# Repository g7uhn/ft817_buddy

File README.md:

# ft817_buddy
A companion display &amp; controls for the FT-817.

This is a work in progess, [more information at my page](http://alloutput.com/ft-817-buddy/).

A little story about the build is over at [SWLing Post](https://swling.com/blog/2020/08/andy-builds-a-genius-companion-control-display-for-the-yaesu-ft-817-transceiver/).

Rev4 hardware files now released :-)

Enjoy!

<br />This work is licensed under a <a rel="license" href="http://creativecommons.org/licenses/by-sa/4.0/">Creative Commons Attribution-ShareAlike 4.0 International License</a>.

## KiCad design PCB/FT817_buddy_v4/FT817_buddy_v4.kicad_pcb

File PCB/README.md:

Rev4 hardware files

<br />This work is licensed under a <a rel="license" href="http://creativecommons.org/licenses/by-sa/4.0/">Creative Commons Attribution-ShareAlike 4.0 International License</a>.

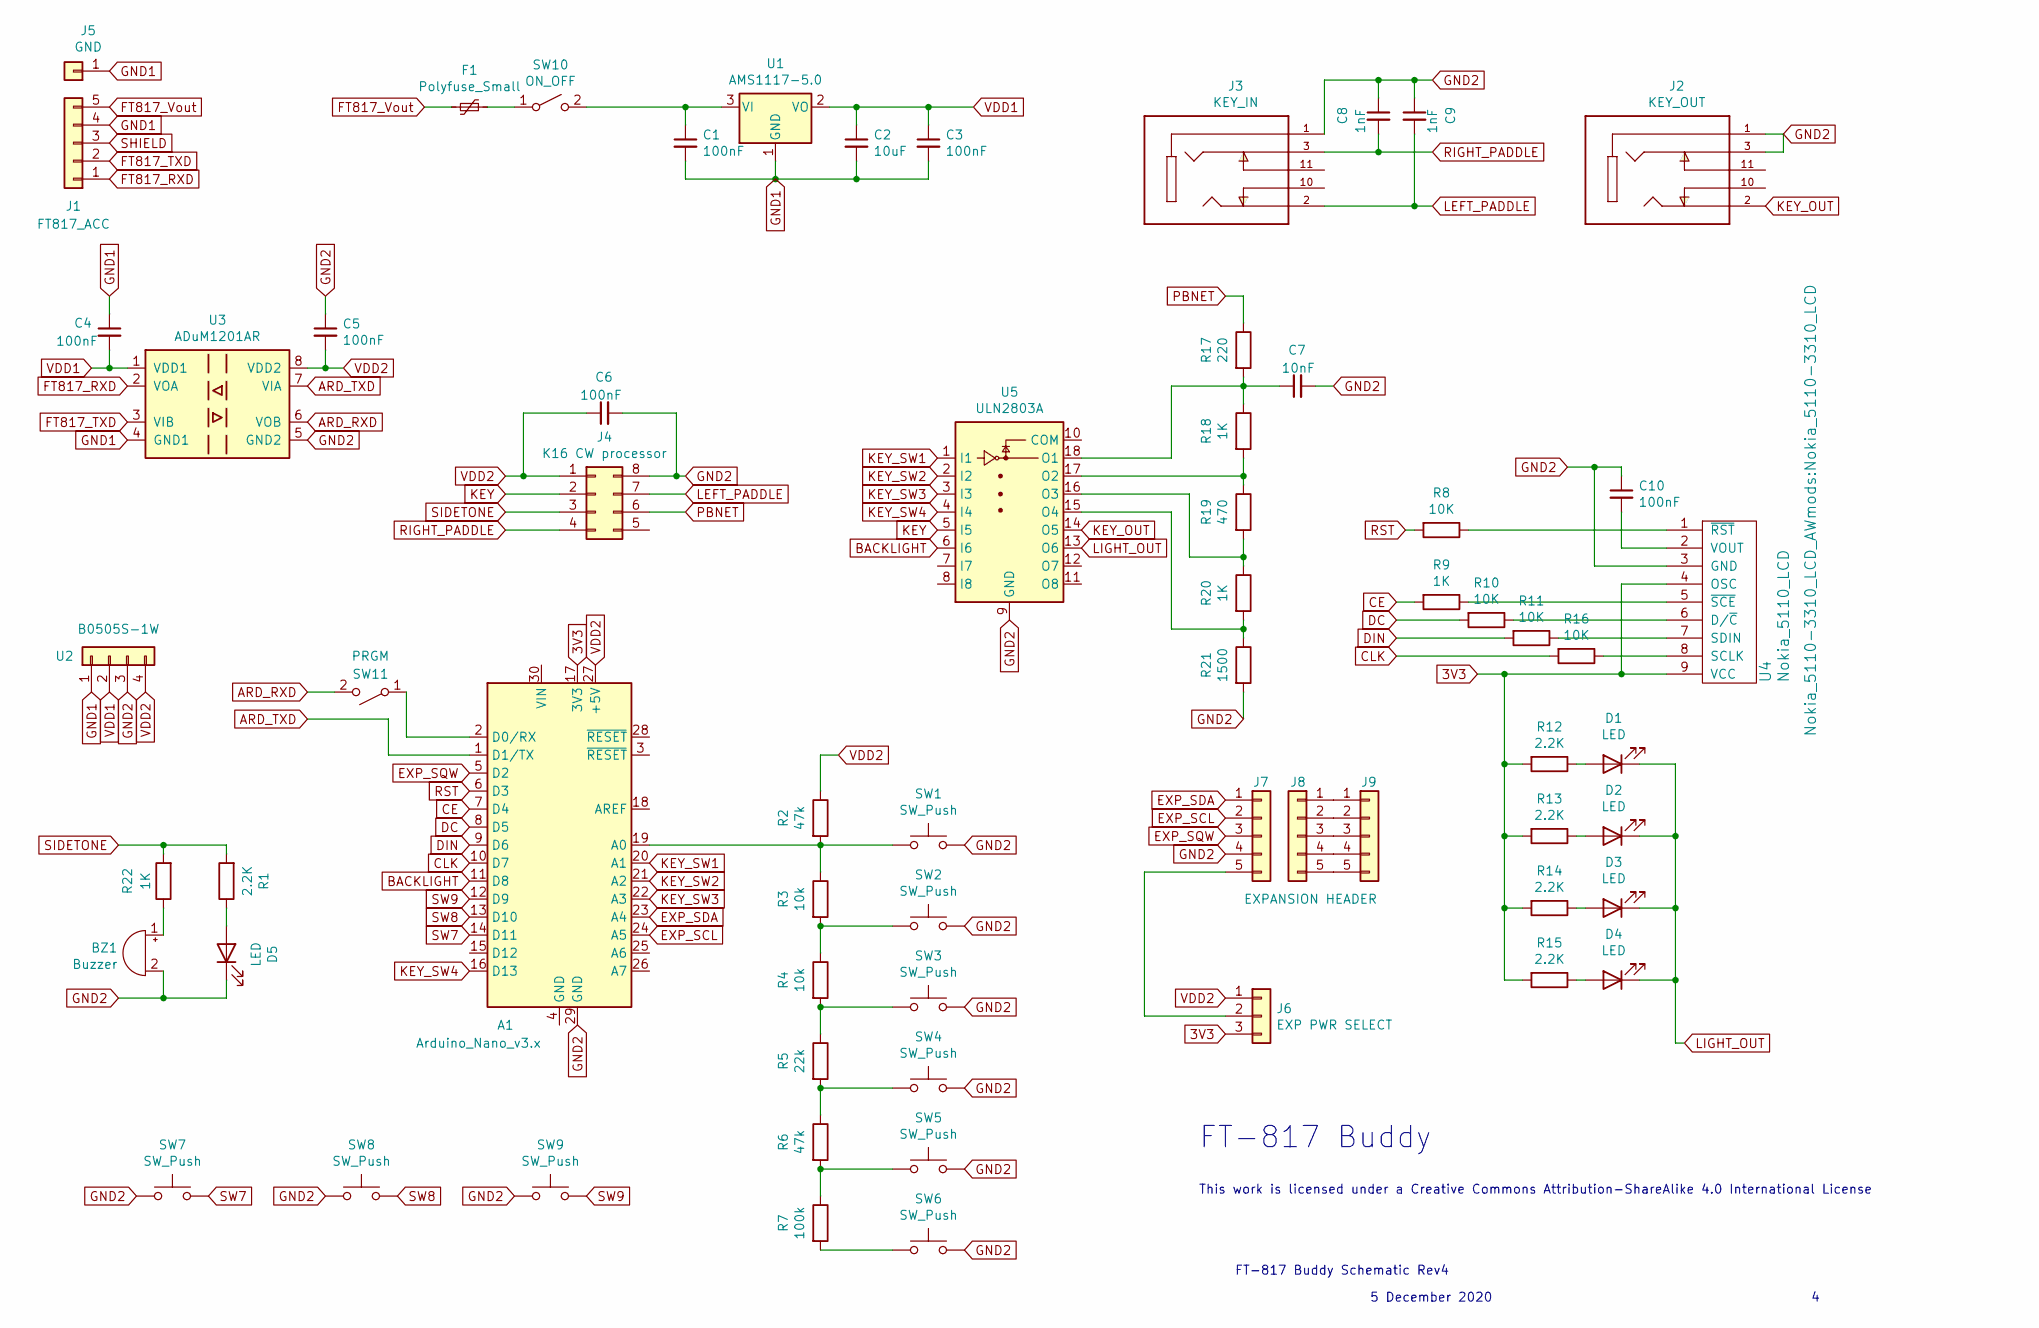
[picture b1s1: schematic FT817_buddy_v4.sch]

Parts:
A1: Arduino_Nano_v3.x; Arduino_Nano
BZ1: Buzzer; Buzzer_Murata_PKMCS0909E4000-R1
C1, C3, C4, C5, C6, C10: 100nF; C_0805_2012Metric_Pad1.15x1.40mm_HandSolder; JLCPCB C49678
C2: 10uF; C_0805_2012Metric_Pad1.15x1.40mm_HandSolder; JLCPCB C15850
C7: 10nF; C_0805_2012Metric_Pad1.15x1.40mm_HandSolder; JLCPCB C1710
C8, C9: 1nF; C_0805_2012Metric_Pad1.15x1.40mm_HandSolder; JLCPCB C46653
D1, D2, D3, D4, D5: LED; LED_0805_2012Metric_Pad1.15x1.40mm_HandSolder
F1: Polyfuse_Small; Fuse_1206_3216Metric_Pad1.42x1.75mm_HandSolder; JLCPCB C369154
J1: FT817_ACC; PinHeader_1x05_P2.54mm_Horizontal
J2: KEY_OUT; CUI_SJ1-3525N; PARTREV 1.02
J3: KEY_IN; CUI_SJ1-3525N; PARTREV 1.02
J4: K16 CW processor; DIP-8_W7.62mm_Socket
J5: GND; PinHeader_1x01_P2.54mm_Vertical
J6: EXP PWR SELECT; PinHeader_1x03_P2.54mm_Vertical
J7, J8: PinHeader_1x05_P2.54mm_Vertical
J9: EXPANSION HEADER; PinSocket_1x05_P2.54mm_Vertical
R1, R12, R13, R14, R15: 2.2K; R_0805_2012Metric_Pad1.15x1.40mm_HandSolder; JLCPCB C17520
R2, R6: 47k; R_0805_2012Metric_Pad1.15x1.40mm_HandSolder; JLCPCB C17713
R3, R4: 10k; R_0805_2012Metric_Pad1.15x1.40mm_HandSolder; JLCPCB C17414
R5: 22k; R_0805_2012Metric_Pad1.15x1.40mm_HandSolder; JLCPCB C17560
R7: 100k; R_0805_2012Metric_Pad1.15x1.40mm_HandSolder; JLCPCB C17407
R8, R10, R11, R16: 10K; R_0805_2012Metric_Pad1.15x1.40mm_HandSolder; JLCPCB C17414
R9, R18, R20, R22: 1K; R_0805_2012Metric_Pad1.15x1.40mm_HandSolder; JLCPCB C17513
R17: 220; R_0805_2012Metric_Pad1.15x1.40mm_HandSolder; JLCPCB C17557
R19: 470; R_0805_2012Metric_Pad1.15x1.40mm_HandSolder; JLCPCB C17710
R21: 1500; R_0805_2012Metric_Pad1.15x1.40mm_HandSolder; JLCPCB C4310
SW1, SW2, SW3, SW4, SW5, SW6, SW7, SW8, SW9: SW_Push; SW_PUSH_6mm
SW10: ON_OFF; SW_Slide_1P2T_CK_OS102011MS2Q
SW11: PRGM; SW_Slide_1P2T_CK_OS102011MS2Q
U1: AMS1117-5.0; SOT-223-3_TabPin2; JLCPCB C6187
U2: B0505S-1W; PinHeader_1x04_P2.54mm_Vertical
U3: ADuM1201AR; SOIC-8_3.9x4.9mm_P1.27mm; JLCPCB C9669
U4: Nokia_5110_LCD; Nokia_5110-3310_LCD
U5: ULN2803A; SOIC-18W_7.5x11.6mm_P1.27mm; JLCPCB C9683

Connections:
3V3: A1.17 (3V3), J6.3, R12.2, R13.2, R14.2, R15.2, U4.4 (OSC), U4.9 (VCC)
ARD_RXD: SW11.2 (B), U3.6 (VOB)
ARD_TXD: A1.1 (D1/TX), U3.7 (VIA)
BACKLIGHT: A1.11 (D8), U5.6 (I6)
CE: A1.7 (D4), R9.2
CLK: A1.10 (D7), R16.2
DC: A1.8 (D5), R10.2
DIN: A1.9 (D6), R11.2
EXP_SCL: A1.24 (A5), J7.2
EXP_SDA: A1.23 (A4), J7.1
EXP_SQW: A1.5 (D2), J7.3
FT817_RXD: J1.1, U3.2 (VOA)
FT817_TXD: J1.2, U3.3 (VIB)
FT817_Vout: F1.2, J1.5
GND1: C1.2, C2.2, C3.2, C4.1, J1.4, J5.1, U1.1 (GND), U2.1, U3.4 (GND1)
GND2: A1.29 (GND), BZ1.2 (+), C5.1, C6.2, C7.2, C8.1, C9.1, C10.1, D5.1 (K), J2.1, J2.3, J3.1, J4.8, J7.4, R21.2, SW1.2, SW2.2, SW3.2, SW4.1, SW5.1, SW6.1, SW7.1, SW8.1, SW9.1, U2.3, U3.5 (GND2), U4.3 (GND), U5.9 (GND)
KEY: J4.2, U5.5 (I5)
KEY_OUT: J2.2, U5.14 (O5)
KEY_SW1: A1.20 (A1), U5.1 (I1)
KEY_SW2: A1.21 (A2), U5.2 (I2)
KEY_SW3: A1.22 (A3), U5.3 (I3)
KEY_SW4: A1.16 (D13), U5.4 (I4)
LEFT_PADDLE: C9.2, J3.2, J4.7
LIGHT_OUT: D1.1 (K), D2.1 (K), D3.1 (K), D4.1 (K), U5.13 (O6)
unnamed: A1.2 (D0/RX), SW11.1 (A)
unnamed: A1.19 (A0), R2.2, R3.1, SW1.1
unnamed: BZ1.1 (-), R22.1
unnamed: C1.1, SW10.2 (B), U1.3 (VI)
unnamed: C7.1, R17.2, R18.1, U5.18 (O1)
unnamed: C10.2, U4.2 (VOUT)
unnamed: D1.2 (A), R12.1
unnamed: D2.2 (A), R13.1
unnamed: D3.2 (A), R14.1
unnamed: D4.2 (A), R15.1
unnamed: D5.2 (A), R1.1
unnamed: F1.1, SW10.1 (A)
unnamed: J6.2, J7.5
unnamed: J8.1, J9.1
unnamed: J8.2, J9.2
unnamed: J8.3, J9.3
unnamed: J8.4, J9.4
unnamed: J8.5, J9.5
unnamed: R3.2, R4.1, SW2.1
unnamed: R4.2, R5.1, SW3.1
unnamed: R5.2, R6.1, SW4.2
unnamed: R6.2, R7.1, SW5.2
unnamed: R7.2, SW6.2
unnamed: R8.1, U4.1 (~RST)
unnamed: R9.1, U4.5 (~SCE)
unnamed: R10.1, U4.6 (D/~C)
unnamed: R11.1, U4.7 (SDIN)
unnamed: R16.1, U4.8 (SCLK)
unnamed: R18.2, R19.1, U5.17 (O2)
unnamed: R19.2, R20.1, U5.16 (O3)
unnamed: R20.2, R21.1, U5.15 (O4)
PBNET: J4.6, R17.1
RIGHT_PADDLE: C8.2, J3.3, J4.4
RST: A1.6 (D3), R8.2
SHIELD: J1.3
SIDETONE: J4.3, R1.2, R22.2
SW7: A1.14 (D11), SW7.2
SW8: A1.13 (D10), SW8.2
SW9: A1.12 (D9), SW9.2
VDD1: C2.1, C3.1, C4.2, U1.2 (VO), U2.2, U3.1 (VDD1)
VDD2: A1.27 (+5V), C5.2, C6.1, J4.1, J6.1, R2.1, U2.4, U3.8 (VDD2)

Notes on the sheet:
This work is licensed under a Creative Commons Attribution-ShareAlike 4.0 International License
FT-817 Buddy Schematic Rev4
5 December 2020
FT-817 Buddy

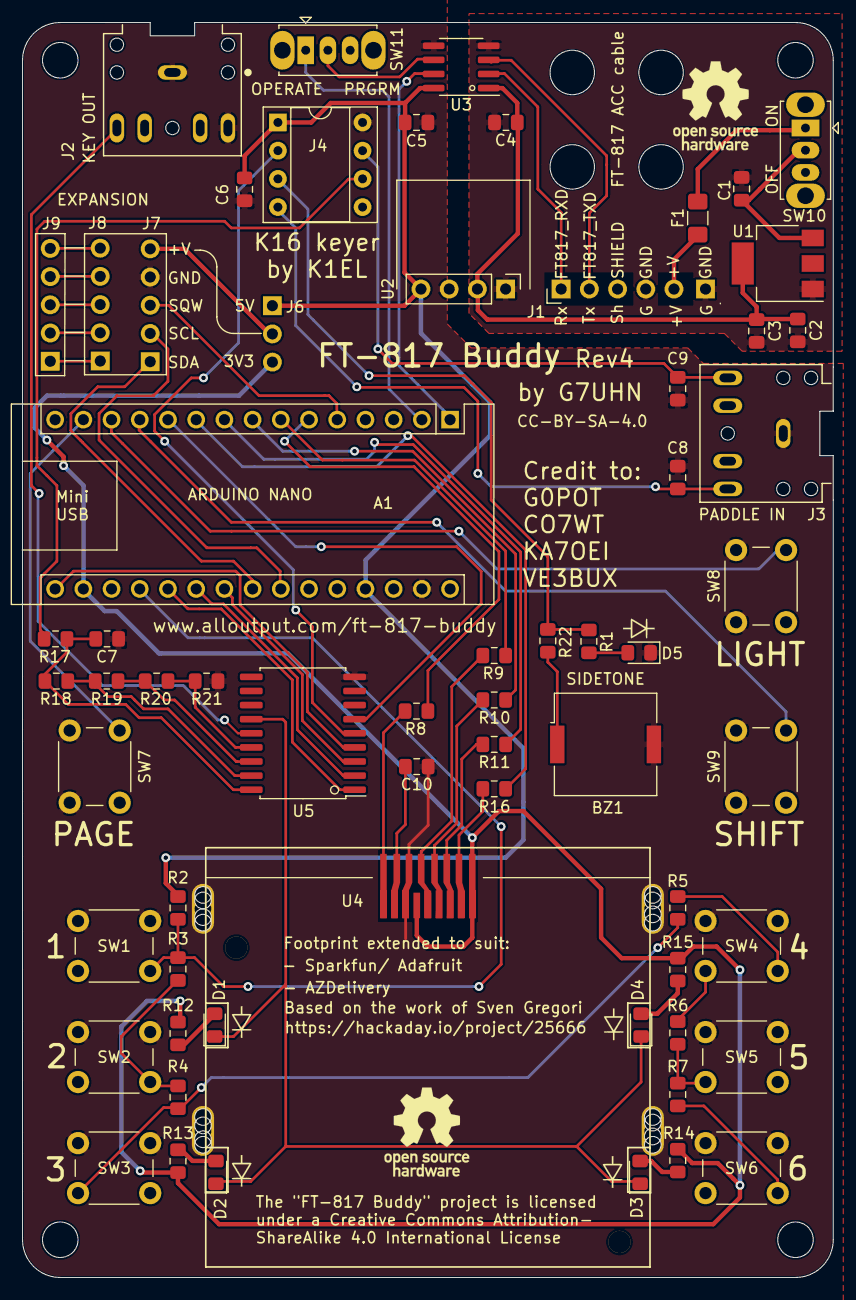
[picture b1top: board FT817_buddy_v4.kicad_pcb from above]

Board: 2 copper layers, 73.0 x 113.0 mm, 70 parts (0 on the bottom side), 64 nets.

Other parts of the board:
 : diode_small
 #2,  #3,  #4,  #5: diode_small

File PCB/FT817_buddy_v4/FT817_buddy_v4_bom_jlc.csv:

"Comment","Designator","Footprint","LCSC Part #"
"100nF","C1,C3,C5,C4,C10,C6","C_0805_2012Metric_Pad1.15x1.40mm_HandSolder","C49678"
"10uF","C2","C_0805_2012Metric_Pad1.15x1.40mm_HandSolder","C15850"
"10nF","C7","C_0805_2012Metric_Pad1.15x1.40mm_HandSolder","C1710"
"1nF","C8,C9","C_0805_2012Metric_Pad1.15x1.40mm_HandSolder","C46653"
"Polyfuse_Small","F1","Fuse_1206_3216Metric_Pad1.42x1.75mm_HandSolder","C369154"
"47k","R2,R6","R_0805_2012Metric_Pad1.15x1.40mm_HandSolder","C17713"
"10k","R3,R4","R_0805_2012Metric_Pad1.15x1.40mm_HandSolder","C17414"
"22k","R5","R_0805_2012Metric_Pad1.15x1.40mm_HandSolder","C17560"
"100k","R7","R_0805_2012Metric_Pad1.15x1.40mm_HandSolder","C17407"
"10K","R8,R10,R11,R16","R_0805_2012Metric_Pad1.15x1.40mm_HandSolder","C17414"
"1K","R9,R18,R20,R22","R_0805_2012Metric_Pad1.15x1.40mm_HandSolder","C17513"
"2.2K","R12,R13,R14,R15,R1","R_0805_2012Metric_Pad1.15x1.40mm_HandSolder","C17520"
"220","R17","R_0805_2012Metric_Pad1.15x1.40mm_HandSolder","C17557"
"470","R19","R_0805_2012Metric_Pad1.15x1.40mm_HandSolder","C17710"
"1500","R21","R_0805_2012Metric_Pad1.15x1.40mm_HandSolder","C4310"
"AMS1117-5.0","U1","SOT-223-3_TabPin2","C6187"
"ADuM1201AR","U3","SOIC-8_3.9x4.9mm_P1.27mm","C9669"
"ULN2803A","U5","SOIC-18W_7.5x11.6mm_P1.27mm","C9683"

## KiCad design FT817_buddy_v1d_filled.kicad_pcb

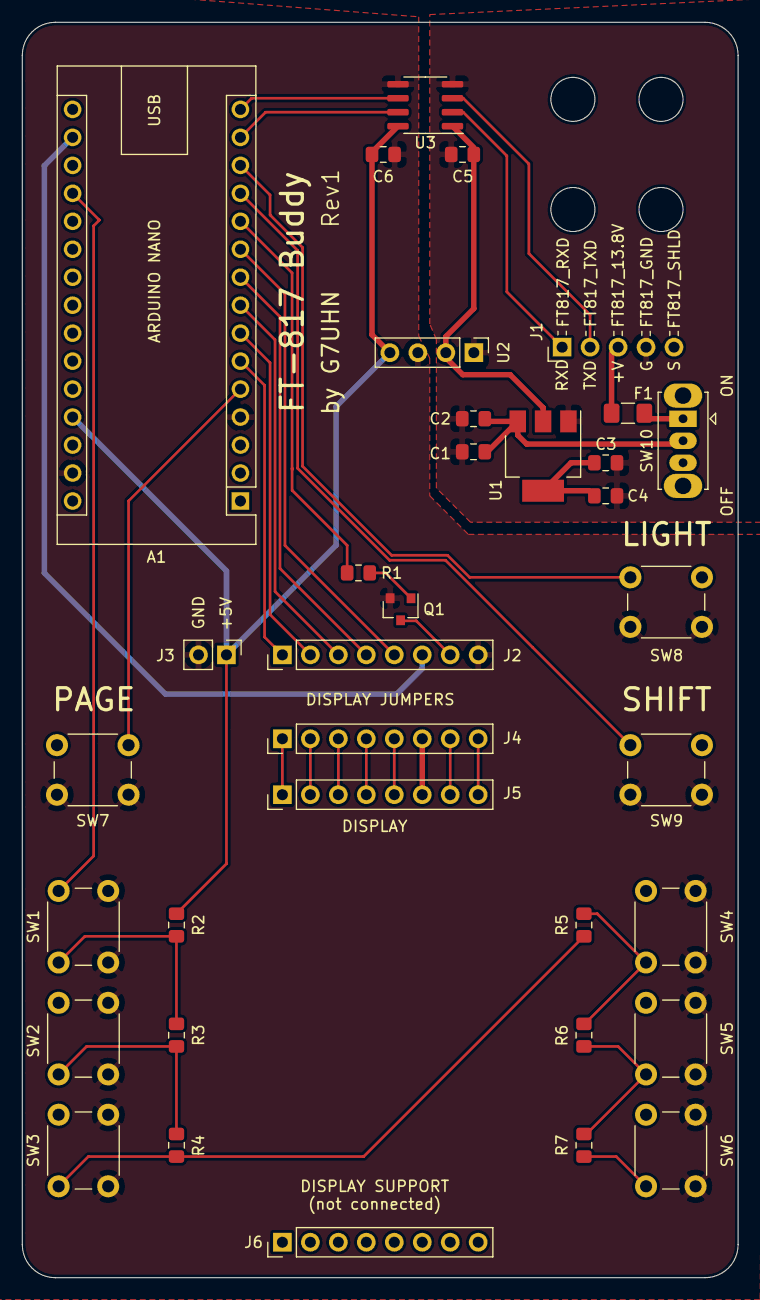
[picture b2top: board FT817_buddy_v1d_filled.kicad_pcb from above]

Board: 2 copper layers, 65.0 x 114.0 mm, 35 parts (0 on the bottom side), 37 nets.

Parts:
A1: Arduino_Nano_v3.x; Arduino_Nano
C1, C3: 10uF; C_0805_2012Metric_Pad1.15x1.40mm_HandSolder
C2, C4, C5, C6: 100nF; C_0805_2012Metric_Pad1.15x1.40mm_HandSolder
F1: Polyfuse_Small; Fuse_1206_3216Metric_Pad1.42x1.75mm_HandSolder
J1: FT817_ACC; PinHeader_1x05_P2.54mm_Horizontal
J2: ARD_SPI; PinHeader_1x08_P2.54mm_Vertical
J3: 5VDC; PinHeader_1x02_P2.54mm_Vertical
J4: DISP_PINS; PinHeader_1x08_P2.54mm_Vertical
J5: DISPLAY; PinHeader_1x08_P2.54mm_Vertical
J6: DISPLAY_SUPPORT; PinHeader_1x08_P2.54mm_Vertical
Q1: BC817; SOT-23
R1: 1k; R_0805_2012Metric_Pad1.15x1.40mm_HandSolder
R2, R6: 47k; R_0805_2012Metric_Pad1.15x1.40mm_HandSolder
R3: 9k1; R_0805_2012Metric_Pad1.15x1.40mm_HandSolder
R4: 15k; R_0805_2012Metric_Pad1.15x1.40mm_HandSolder
R5: 24k; R_0805_2012Metric_Pad1.15x1.40mm_HandSolder
R7: 150k; R_0805_2012Metric_Pad1.15x1.40mm_HandSolder
SW1, SW2, SW3, SW4, SW5, SW6, SW7, SW8, SW9: SW_Push; SW_PUSH_6mm
SW10: ON_OFF; SW_Slide_1P2T_CK_OS102011MS2Q
U1: AP1117-50; SOT-223-3_TabPin2
U2: B0505S-1W; PinHeader_1x04_P2.54mm_Vertical
U3: ADuM1201AR; SOIC-8_3.9x4.9mm_P1.27mm

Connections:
3V3: A1.17, J2.6
ARD_RXD: A1.15, U3.6
ARD_TXD: A1.14, U3.7
BACKLIGHT: A1.11, R1.2
CE: A1.7, J2.2
CLK: A1.10, J2.5
DC: A1.8, J2.3
DIN: A1.9, J2.4
FT817_RXD: J1.1, U3.2
FT817_TXD: J1.2, U3.3
FT817_Vout: F1.2, J1.3
GND1: C1.2, C2.2, C3.2, C4.2, C5.1, J1.4, U1.1, U2.1, U3.4
GND2: A1.4, A1.29, C6.1, J2.8, J3.2, Q1.2, SW1.2, SW2.2, SW3.2, SW4.2, SW5.2, SW6.2, SW7.1, SW8.1, SW9.1, U2.3, U3.5
unnamed: A1.19, R2.2, R3.1, SW1.1
unnamed: C1.1, C2.1, SW10.2, U1.3
unnamed: F1.1, SW10.1
unnamed: J2.7, Q1.3
unnamed: J4.1, J5.1
unnamed: J4.2, J5.2
unnamed: J4.3, J5.3
unnamed: J4.4, J5.4
unnamed: J4.5, J5.5
unnamed: J4.6, J5.6
unnamed: J4.7, J5.7
unnamed: J4.8, J5.8
unnamed: Q1.1, R1.1
unnamed: R3.2, R4.1, SW2.1
unnamed: R4.2, R5.1, SW3.1
unnamed: R5.2, R6.1, SW4.1
unnamed: R6.2, R7.1, SW5.1
unnamed: R7.2, SW6.1
RST: A1.6, J2.1
SW7: A1.5, SW7.2
SW8: A1.13, SW8.2
SW9: A1.12, SW9.2
VDD1: C3.1, C4.1, C5.2, U1.2, U2.2, U3.1
VDD2: A1.27, C6.2, J3.1, R2.1, U2.4, U3.8

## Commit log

2020-10-17 improved src code using CO7WT's ft817 library
2020-10-17 main sketch housekeeping
2020-10-17 latest info
2020-10-17 added platformio.ini
2020-10-17 platformIO housekeeping
2020-10-17 added include folder
2020-10-17 added second page of soft-keys
2020-10-17 added toggleRfSql() function
2020-10-17 added some page1 functions, tidied user function calls
2020-10-17 bug fix, removed debug print statements
2020-10-18 Update main.cpp
    Commented out "opt in" statement on EEPROM writes
2020-10-18 added "fast refresh" loop within main loop
2020-10-18 moved displayABCkeys() into slow refresh loop
2020-10-18 Added status indicators against softkey labels
2020-10-18 added NeoSWSerial to included libs
2020-10-18 moved PAGE and LIGHT buttons into slow loop
2020-10-18 Reduced delays to smooth operation
2020-10-18 Added setKeyerSpeed function
2020-10-18 Removed debug print statements
2020-10-20 fixed serial baud from int to long to allow 38400
2020-10-20 silenced mode read error
2020-10-25 Code modified for Arduino Pro Mini
2020-11-08 Updated platformio.ini to include both boards
2020-11-08 Revert "Merge Development into Master"
2020-11-08 Unmuted "???" print for mode read error
2020-11-08 Unmunted "???" for mode read error
2020-11-08 Unmuted "???" on mode read error
2020-11-09 Rebaselined for Rev2 hardware
2020-11-09 Commented out "opt in" to EEPROM_WRITES
2020-11-10 Hardware files removed pending Rev2 release
2020-11-11 Changed backlight to toggle operation
2020-11-11 Improved backlight - timed and toggle
2020-11-14 Added keyer pin defines
2020-11-14 Added Keyer push button functions
2020-11-15 Tidied up comments in ft817 lib
2020-11-16 Fixed "opt in" statement
2020-11-16 Tightened up risk statement
2020-11-21 Added Creative Commons license statement
2020-11-26 Moved displayABCkeys to once on Arduino setup
2020-11-27 SoftKey status to triggered, buttons to fast loop
2020-11-27 Set to Pro Mini
2020-11-27 Updated opt-in
2020-11-28 Added current features to README
2020-11-28 Added more features
2020-11-28 fixed sub-bullets?
2020-11-29 Updated license statement with links
2020-11-29 Updated license text
2020-12-02 Allowed EEPROM writes, board = Nano
2020-12-02 Shuffled Page 3 soft-keys
2020-12-04 Improved keyer function names and comments
2020-12-06 Commented opt-in statement
2020-12-06 Commented against all EEPROM reads and writes
2020-12-12 Added PCB folder
2020-12-13 Corrected ft817.h case
2020-12-30 added new software serial port
2020-12-30 moved main display draw to function
2020-12-30 OK EEPROM writes while developing this branch
2020-12-30 introduced expansion page
2020-12-30 Updated abcKeys to work as single-shot
2020-12-30 fix drawMainDisplay + softKeyStatus on page change
2020-12-30 Reposition placeholder text
2020-12-30 Added time value on all pages
2020-12-30 added uptime counter clock
2020-12-30 added clock setting buttons
2020-12-30 Improved clock setting process
2020-12-30 changed page2 soft-keys
2020-12-30 updated int. keyer speed prefs, moved clock reset
2020-12-30 corrected millis values on minutes tickOver
2020-12-30 corrected missing spaces on page 2 labels
2020-12-30 commented out opt-in statement for GitHub release
2020-12-30 Position of time display shifted down 1px
2020-12-30 Added clock to features
2020-12-30 Re-ordered hhmm setting buttons to make more sense
2021-02-06 uncomment/allow EEPROM changes
2021-02-06 changed pin assignments
2021-02-06 added SparkFun DS1307 lib to repo
2021-02-06 RTC set and get added
2021-02-07 Increment time from RTC square wave interrupt
2021-02-07 fixed counting error
2021-02-17 Improved comments on soft-key functions
2021-02-27 tidying up
2021-02-27 Rev4 released
2021-02-27 Added pdf schematic
2021-03-20 added "comment/uncomment" comment for RTC module
2021-03-20 Opt-in comments set for public repo
2021-03-20 includes fixed with new workspace?
2021-03-20 Removed rogue folder
2021-03-20 Updated with input/ouput and not connected symbols
2021-03-20 Moved EEPROM reminder to setup()
2021-03-20 Changed read buttonStatus to switch/case
2021-04-03 Added 1:1 PCB outline as drilling template
2021-04-24 Added enclosure base STL

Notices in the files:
PCB/FT817_buddy_v4/FT817_buddy_v4.kicad_pcb:
CC-BY-SA-4.0
